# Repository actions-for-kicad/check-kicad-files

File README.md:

# check-kicad-files

> ⚠️ **This repository is archived and no longer maintained.**  
> Please use my new and improved all in one [KiCad action](https://github.com/marketplace/actions/kicad-actions).

ERC and DRC test for KiCad files.

> **_NOTE:_** Minimal KiCad version is 8.0.

# Usage

See [action.yml](action.yml)

```yaml
steps:
  - uses: actions/checkout@v4
  - uses: actions-for-kicad/setup-kicad@v1
    with:
      version: "9.0"
  - uses: actions-for-kicad/check-kicad-files@v1
    with:
      file: "./file.kicad_sch"
      type: "erc"
```

## Inputs

### `file`

Required: `True`

Description: The location to the schematic or PCB file.

### `type`

Required: `True`

Check type, choose one of the following:

- erc
- drc

# License

The scripts and documentation in this project are released under the [GNU license](LICENSE).

# Contributions

Contributions are welcome! Please help me expand and maintain this repository.

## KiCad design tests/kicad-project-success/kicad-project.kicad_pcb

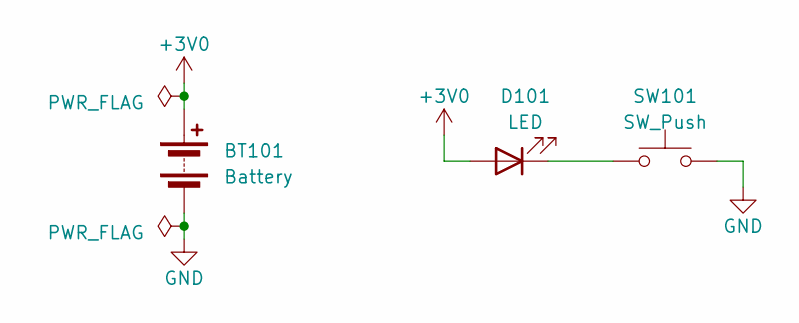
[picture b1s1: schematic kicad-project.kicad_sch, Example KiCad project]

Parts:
BT101: Battery; BatteryHolder_Bulgin_BX0036_1xC
D101: LED; LED_D3.0mm_Horizontal_O1.27mm_Z2.0mm
SW101: SW_Push; SW_PUSH_6mm

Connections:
+3V0: BT101.1 (+), D101.2 (A)
GND: BT101.2 (-), SW101.2
unnamed: D101.1 (K), SW101.1

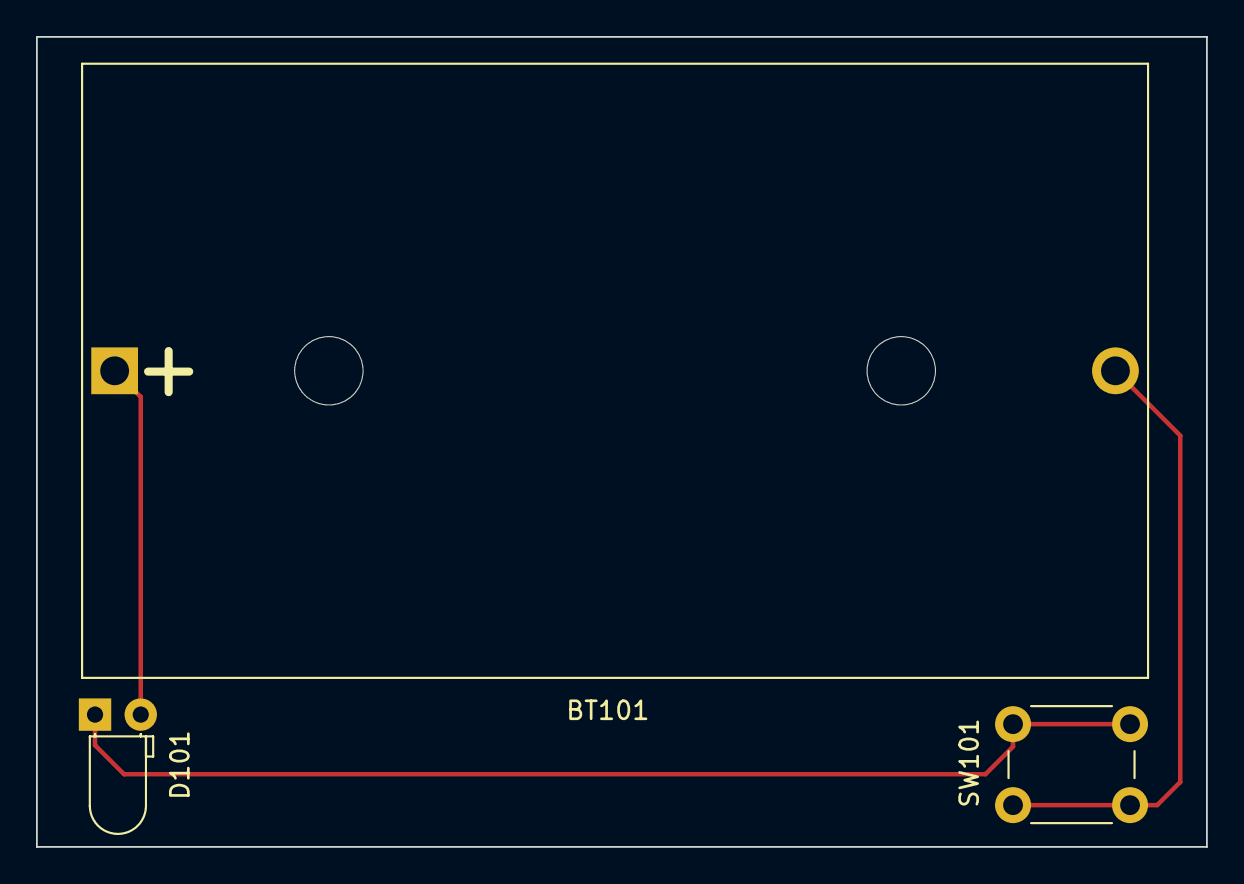
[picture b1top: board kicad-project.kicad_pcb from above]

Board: 2 copper layers, 65.0 x 45.0 mm, 3 parts (0 on the bottom side), 3 nets.

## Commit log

2024-12-27 First commit with setup
2024-12-27 Fixed bug in scrip running
2024-12-27 Fixed test
2024-12-27 Added some debug code
2024-12-27 Fixed debug code
2024-12-27 Fixed tests
2024-12-27 Updated tests
2024-12-27 Added more debug info
2024-12-27 Tried to fix tests
2024-12-27 Finel test to fix library issue
2024-12-27 Reverted schematic update
2024-12-27 Fixed led
2024-12-27 Final test
2024-12-27 Main version tag now uses force
2024-12-27 Updated the readme
2025-03-31 Added version 9.0
